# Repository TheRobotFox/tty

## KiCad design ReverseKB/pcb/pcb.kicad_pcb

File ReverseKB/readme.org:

#+title: Pins

* Ribbon Cable
- Grouding only PIN 4 turn on lamps
- 5 -> 4
- Wired left to right (1->q->a->2->y->2-> ...)
- Folding ribbon cable 6cm space

8 22
7 16
10 16
14 16
10 17
14 17
10 18
14 18
10 19
14 19
10 20
14 20
10 21
10 23
14 23
10 22
8 16
12 16
8 17
12 17
8 18
12 18
8 19
12 19
8 20
12 20
8 21
12 21
8 23
14 22
12 22
9 16
13 16
9 17
13 17
9 18
13 18
9 19
13 19
9 20
13 20
9 21 
13 21 
12 23 
3 15 
11 16 
7 17 
11 17
7 18
11 18
7 19
11 19
7 20
11 20
7 21
3 15
13 23
7 23
0 15
1 15
9 23
11 21
11 23

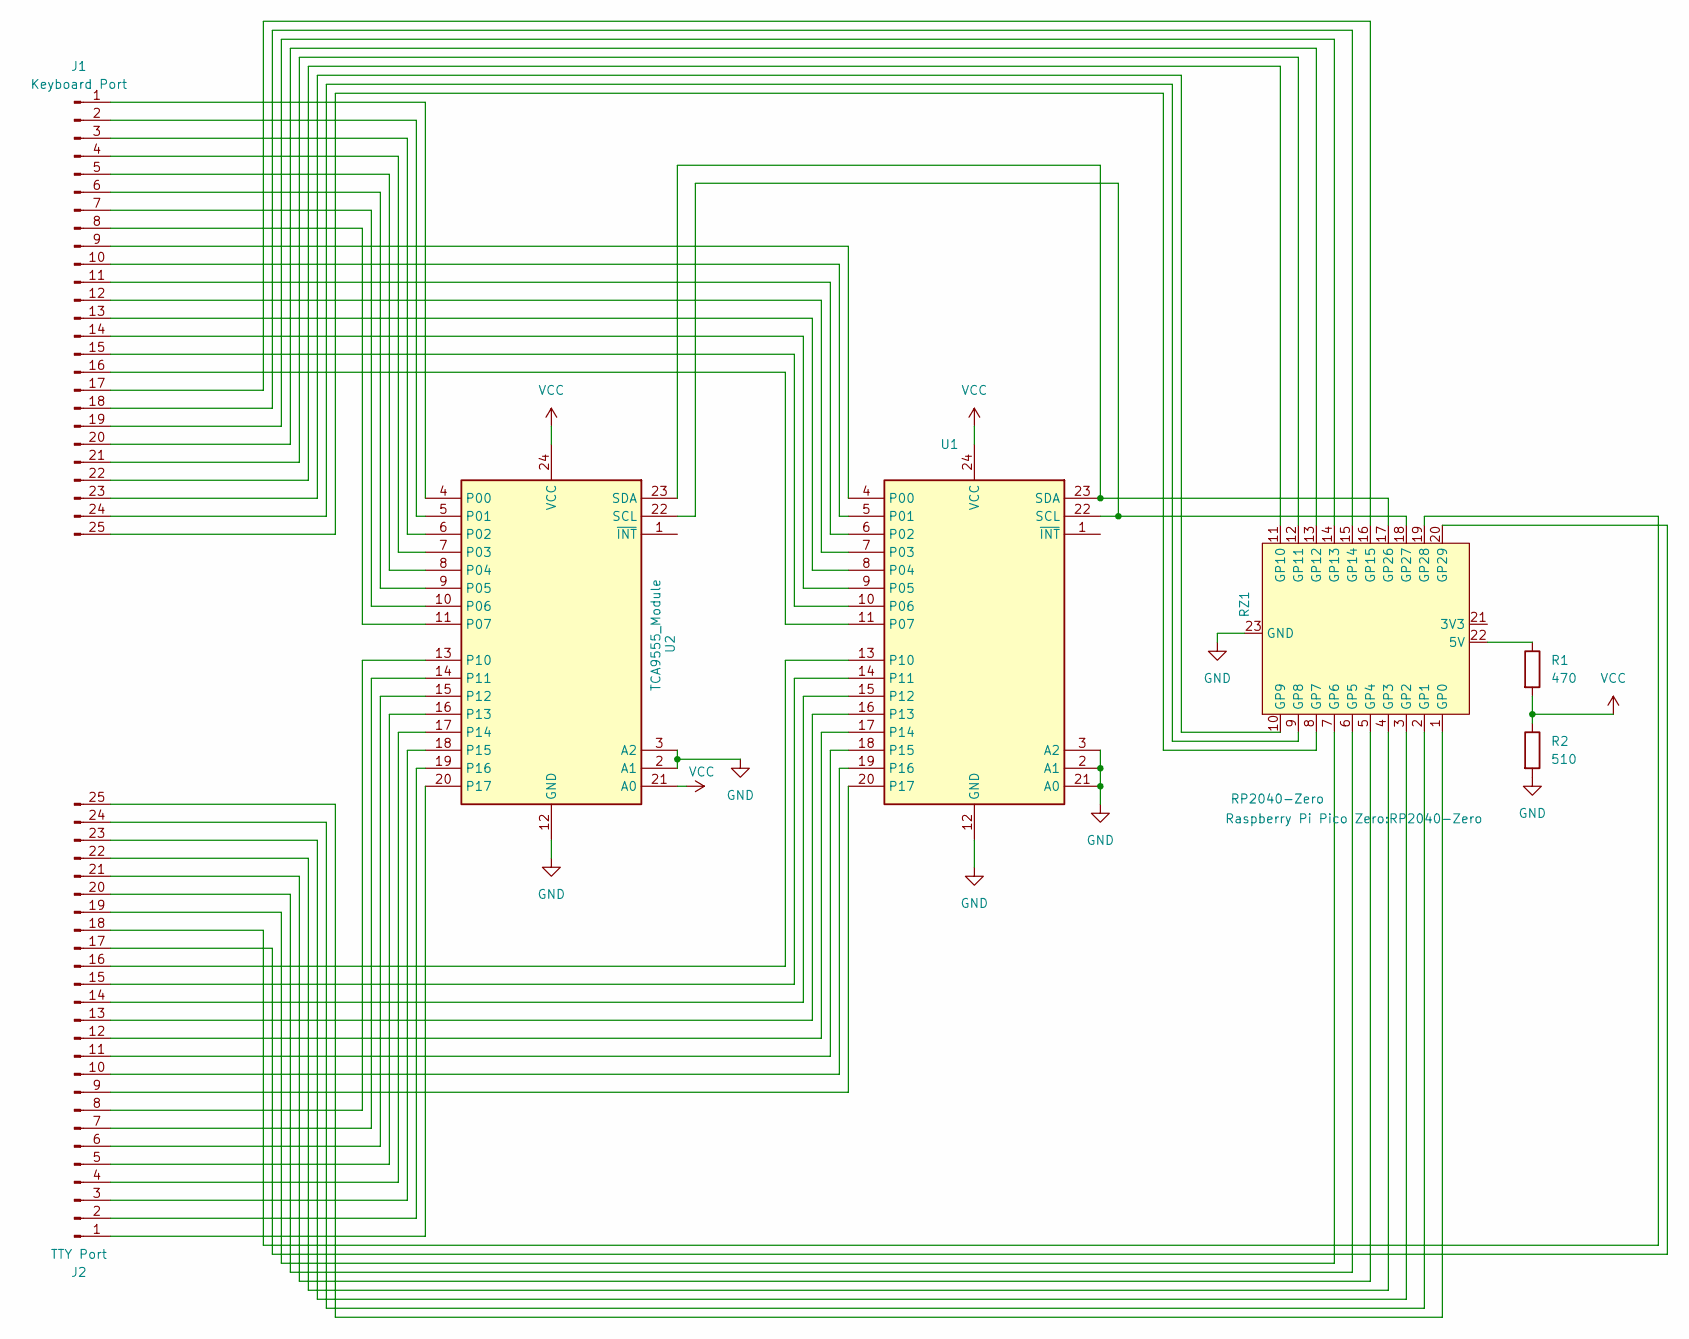
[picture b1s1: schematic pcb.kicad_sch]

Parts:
J1: Keyboard Port; PinHeader_1x25_P2.54mm_Horizontal
J2: TTY Port; PinHeader_1x25_P2.54mm_Vertical
R1: 470; R_Axial_DIN0516_L15.5mm_D5.0mm_P20.32mm_Horizontal
R2: 510; R_Axial_DIN0516_L15.5mm_D5.0mm_P20.32mm_Horizontal
RZ1: RP2040-Zero
U1, U2: TCA9555_Module

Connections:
GND: R2.2, RZ1.23 (GND), U1.2 (A1), U1.3 (A2), U1.12 (GND), U1.21 (A0), U2.2 (A1), U2.3 (A2), U2.12 (GND)
unnamed: J1.1, U2.4 (P00)
unnamed: J1.2, U2.5 (P01)
unnamed: J1.3, U2.6 (P02)
unnamed: J1.4, U2.7 (P03)
unnamed: J1.5, U2.8 (P04)
unnamed: J1.6, U2.9 (P05)
unnamed: J1.7, U2.10 (P06)
unnamed: J1.8, U2.11 (P07)
unnamed: J1.9, U1.4 (P00)
unnamed: J1.10, U1.5 (P01)
unnamed: J1.11, U1.6 (P02)
unnamed: J1.12, U1.7 (P03)
unnamed: J1.13, U1.8 (P04)
unnamed: J1.14, U1.9 (P05)
unnamed: J1.15, U1.10 (P06)
unnamed: J1.16, U1.11 (P07)
unnamed: J1.17, RZ1.16 (GP15)
unnamed: J1.18, RZ1.15 (GP14)
unnamed: J1.19, RZ1.14 (GP13)
unnamed: J1.20, RZ1.13 (GP12)
unnamed: J1.21, RZ1.12 (GP11)
unnamed: J1.22, RZ1.11 (GP10)
unnamed: J1.23, RZ1.10 (GP9)
unnamed: J1.24, RZ1.9 (GP8)
unnamed: J1.25, RZ1.8 (GP7)
unnamed: J2.1, U2.20 (P17)
unnamed: J2.2, U2.19 (P16)
unnamed: J2.3, U2.18 (P15)
unnamed: J2.4, U2.17 (P14)
unnamed: J2.5, U2.16 (P13)
unnamed: J2.6, U2.15 (P12)
unnamed: J2.7, U2.14 (P11)
unnamed: J2.8, U2.13 (P10)
unnamed: J2.9, U1.20 (P17)
unnamed: J2.10, U1.19 (P16)
unnamed: J2.11, U1.18 (P15)
unnamed: J2.12, U1.17 (P14)
unnamed: J2.13, U1.16 (P13)
unnamed: J2.14, U1.15 (P12)
unnamed: J2.15, U1.14 (P11)
unnamed: J2.16, U1.13 (P10)
unnamed: J2.17, RZ1.20 (GP29)
unnamed: J2.18, RZ1.19 (GP28)
unnamed: J2.19, RZ1.7 (GP6)
unnamed: J2.20, RZ1.6 (GP5)
unnamed: J2.21, RZ1.5 (GP4)
unnamed: J2.22, RZ1.4 (GP3)
unnamed: J2.23, RZ1.3 (GP2)
unnamed: J2.24, RZ1.2 (GP1)
unnamed: J2.25, RZ1.1 (GP0)
unnamed: R1.1, RZ1.22 (5V)
unnamed: RZ1.17 (GP26), U1.23 (SDA), U2.23 (SDA)
unnamed: RZ1.18 (GP27), U1.22 (SCL), U2.22 (SCL)
VCC: R1.2, R2.1, U1.24 (VCC), U2.21 (A0), U2.24 (VCC)

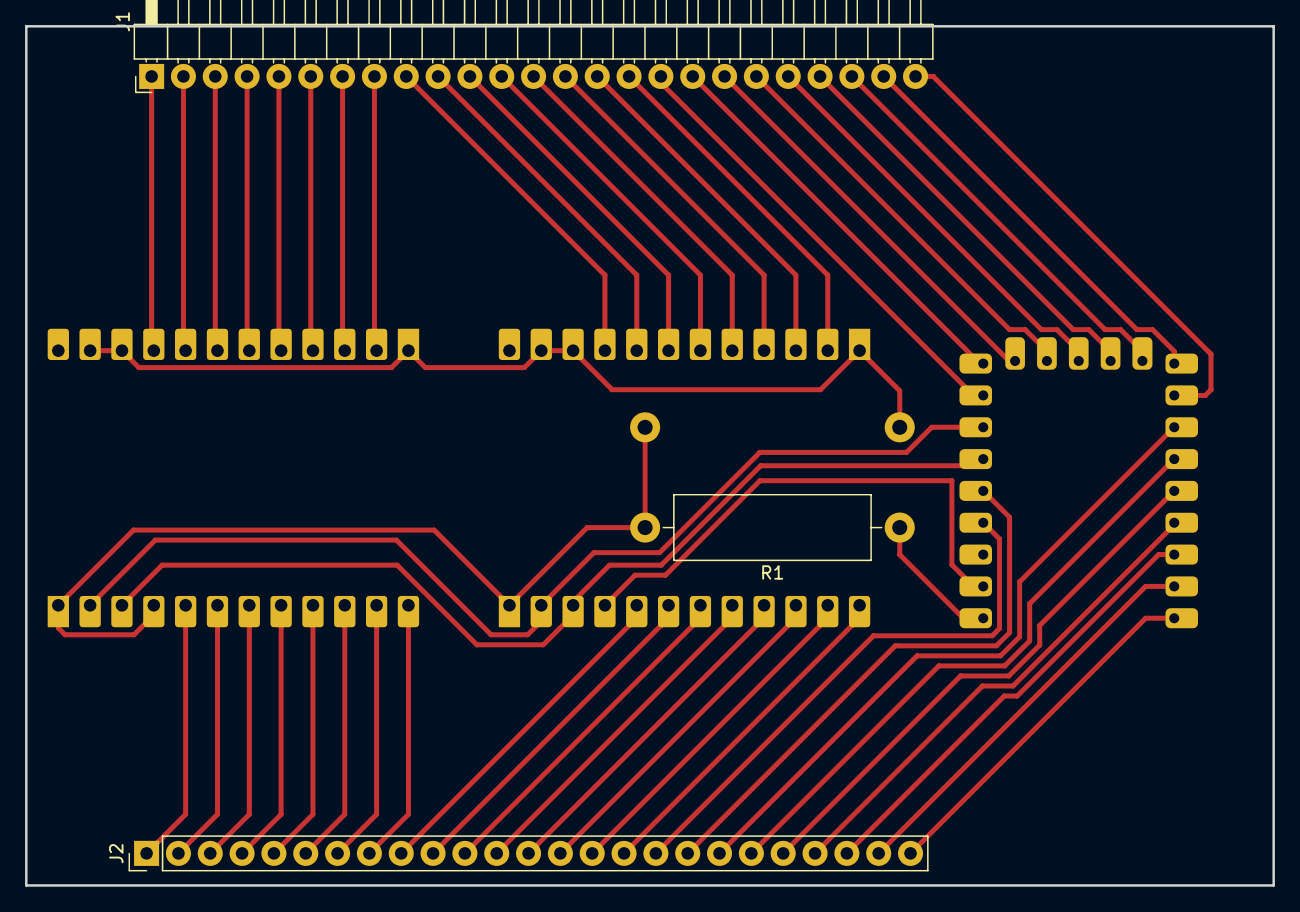
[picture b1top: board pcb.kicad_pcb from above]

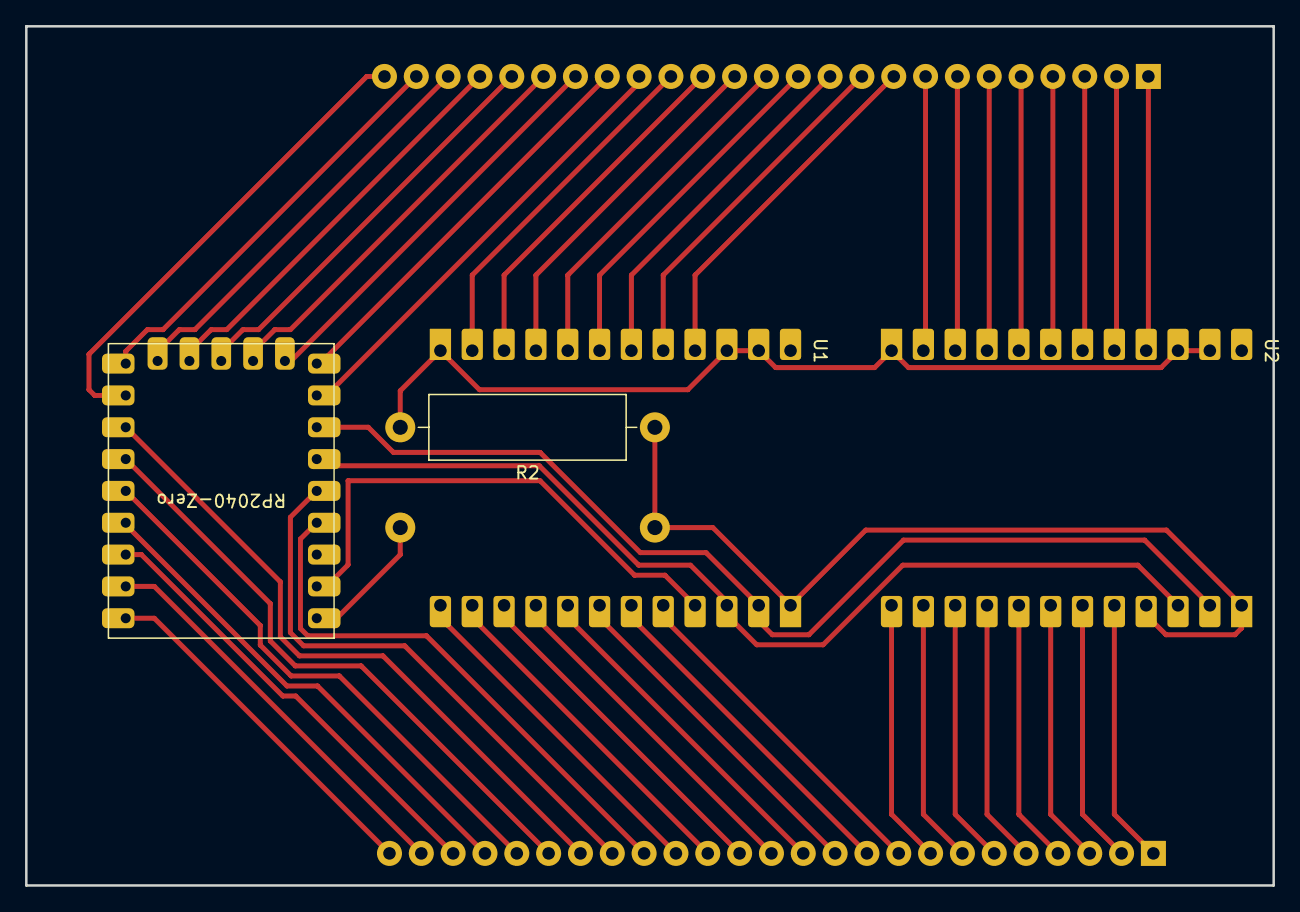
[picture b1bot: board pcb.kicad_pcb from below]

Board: 2 copper layers, 99.5 x 68.6 mm, 7 parts (4 on the bottom side), 55 nets.

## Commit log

2025-04-14 Keyboard
2025-04-28 pcb + driver
